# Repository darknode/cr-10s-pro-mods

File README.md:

# Creality CR-10S Pro hardware mods
### Boards
* [Ribbon cable breakdown board](RibbonCable_MB_BreakdownBoard/) - is fully compatible with original transfer board, helps with wiring with non-original motherboards.

* [Ribbon cable breakdown board (pt)](RibbonCable_MB_BreakdownBoard_pt/) - "pig tail" soldering oriented, semi compatible with original transfer board, but fully compatible with [Transfer board](Transfer_Board/). Has dedicated 4-wire connection for BLTouch and 3-wire connector for LED.

* [Transfer board](Transfer_Board/) - clean transfer board, compatible with [Ribbon cable breakdown board (pt)](RibbonCable_MB_BreakdownBoard_pt/).

#### Wiring examples
*Coming soon*

#### Ready made boards
*Photos coming soon*

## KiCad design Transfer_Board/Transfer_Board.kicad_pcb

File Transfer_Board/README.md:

# Transfer board
Clean transfer board, compatible with [Ribbon cable breakdown board (pt)](../RibbonCable_MB_BreakdownBoard_pt/)

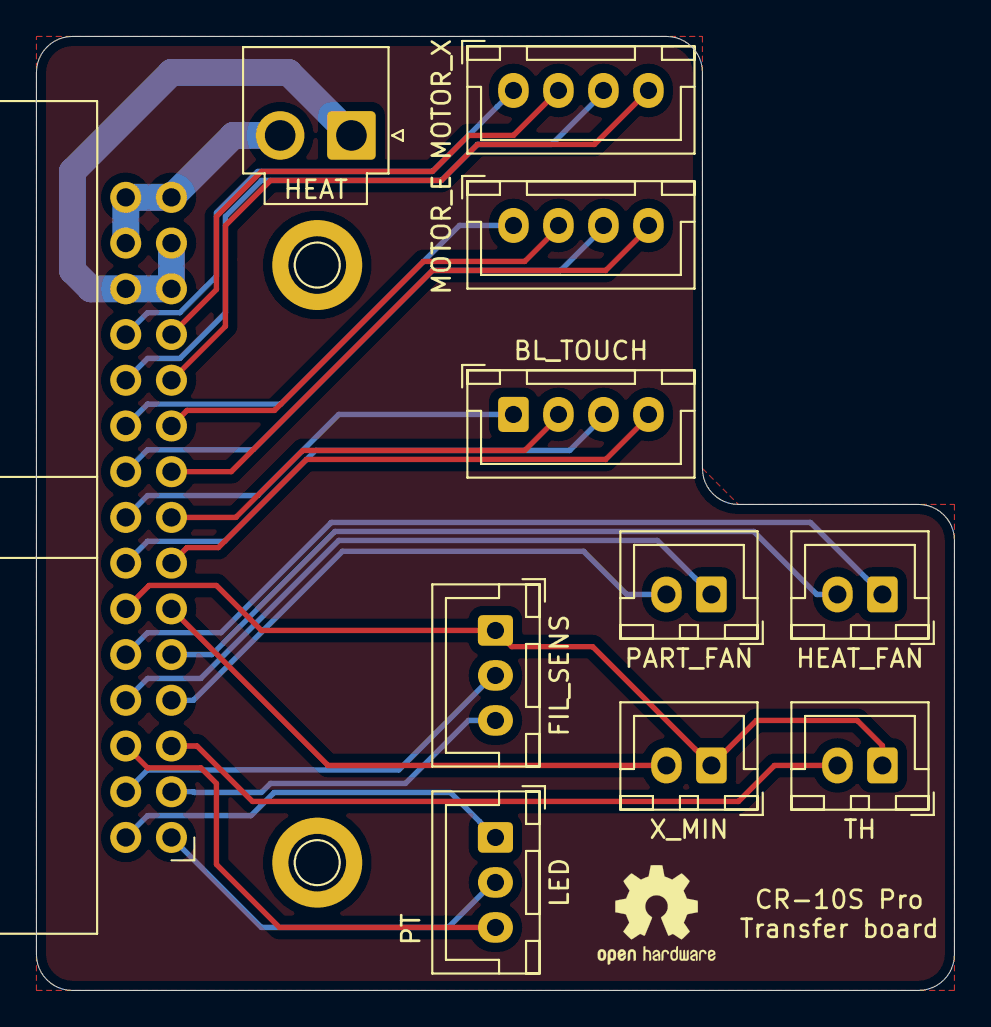
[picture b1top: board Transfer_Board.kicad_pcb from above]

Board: 2 copper layers, 51.0 x 53.0 mm, 11 parts (0 on the bottom side), 26 nets.

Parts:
BL_TOUCH: Conn_01x04; JST_XH_B4B-XH-A_1x04_P2.50mm_Vertical
FIL_SENS: Conn_01x03; JST_XH_B3B-XH-A_1x03_P2.50mm_Vertical
HEAT: Conn_01x02; JST_VH_B2P-VH-B_1x02_P3.96mm_Vertical
HEAT_FAN: Conn_01x02; JST_XH_B2B-XH-A_1x02_P2.50mm_Vertical
LED: Conn_01x03; JST_XH_B3B-XH-A_1x03_P2.50mm_Vertical
MOTOR_E: Conn_01x04; JST_XH_B4B-XH-A_1x04_P2.50mm_Vertical
MOTOR_X: Conn_01x04; JST_XH_B4B-XH-A_1x04_P2.50mm_Vertical
PART_FAN: Conn_01x02; JST_XH_B2B-XH-A_1x02_P2.50mm_Vertical
RIBBON1: Conn_02x15_Odd_Even; IDC-Header_2x15_P2.54mm_Horizontal
TH: Conn_01x02; JST_XH_B2B-XH-A_1x02_P2.50mm_Vertical
X_MIN: Conn_01x02; JST_XH_B2B-XH-A_1x02_P2.50mm_Vertical

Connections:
unnamed: BL_TOUCH.1, RIBBON1.16
unnamed: BL_TOUCH.2, RIBBON1.15
unnamed: BL_TOUCH.3, RIBBON1.14
unnamed: BL_TOUCH.4, RIBBON1.13
unnamed: FIL_SENS.1, RIBBON1.12, TH.1, X_MIN.1
unnamed: FIL_SENS.2, RIBBON1.4
unnamed: FIL_SENS.3, RIBBON1.3
unnamed: HEAT.1, RIBBON1.25, RIBBON1.26, RIBBON1.27
unnamed: HEAT.2, RIBBON1.28, RIBBON1.29, RIBBON1.30
unnamed: HEAT_FAN.1, RIBBON1.10
unnamed: HEAT_FAN.2, RIBBON1.9
unnamed: LED.1, RIBBON1.2
unnamed: LED.2, RIBBON1.1
unnamed: LED.3, RIBBON1.6
unnamed: MOTOR_E.1, RIBBON1.20
unnamed: MOTOR_E.2, RIBBON1.19
unnamed: MOTOR_E.3, RIBBON1.18
unnamed: MOTOR_E.4, RIBBON1.17
unnamed: MOTOR_X.1, RIBBON1.24
unnamed: MOTOR_X.2, RIBBON1.23
unnamed: MOTOR_X.3, RIBBON1.22
unnamed: MOTOR_X.4, RIBBON1.21
unnamed: PART_FAN.1, RIBBON1.8
unnamed: PART_FAN.2, RIBBON1.7
unnamed: RIBBON1.5, TH.2
unnamed: RIBBON1.11, X_MIN.2

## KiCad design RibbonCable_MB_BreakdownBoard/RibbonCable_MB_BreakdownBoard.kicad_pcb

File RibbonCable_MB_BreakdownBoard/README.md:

# Ribbon cable breakdown board
It is fully compatible with [original transfer board](https://www.aliexpress.com/item/33040303019.html), helps with wiring with non-original motherboards.

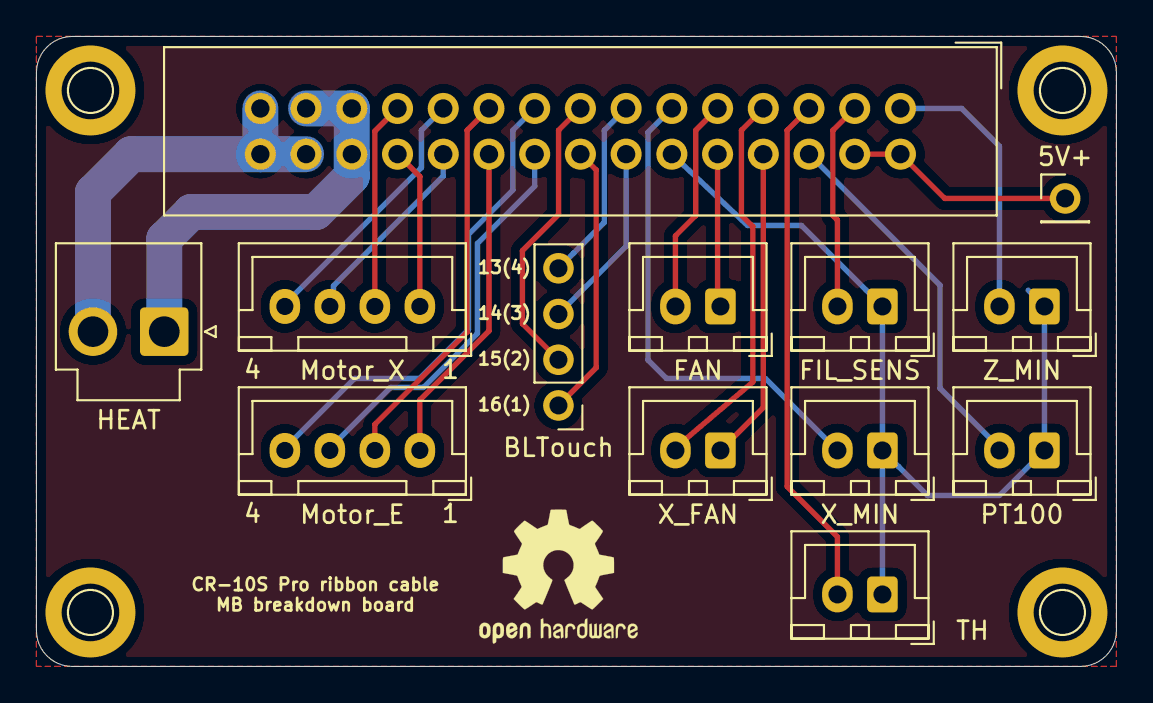
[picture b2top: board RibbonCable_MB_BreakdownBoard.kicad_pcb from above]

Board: 2 copper layers, 60.0 x 35.0 mm, 13 parts (0 on the bottom side), 25 nets.

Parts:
5V+: Conn_01x01; PinHeader_1x01_P2.54mm_Vertical
BLTouch: Conn_01x04; PinHeader_1x04_P2.54mm_Vertical
FAN: Conn_01x02; JST_XH_B2B-XH-A_1x02_P2.50mm_Vertical
FIL_SENS: FIL_SENS; JST_XH_B2B-XH-A_1x02_P2.50mm_Vertical
HEAT: Conn_01x02; JST_VH_B2P-VH-B_1x02_P3.96mm_Vertical
Motor_E: Conn_01x04; JST_XH_B4B-XH-A_1x04_P2.50mm_Vertical
Motor_X: Conn_01x04; JST_XH_B4B-XH-A_1x04_P2.50mm_Vertical
PT100: PT100; JST_XH_B2B-XH-A_1x02_P2.50mm_Vertical
Ribbon1: Ribbon30; IDC-Header_2x15_P2.54mm_Vertical
TH: TH+; JST_XH_B2B-XH-A_1x02_P2.50mm_Vertical
X_FAN: Conn_01x02; JST_XH_B2B-XH-A_1x02_P2.50mm_Vertical
X_MIN: Conn_01x02; JST_XH_B2B-XH-A_1x02_P2.50mm_Vertical
Z_MIN: Z_MIN; JST_XH_B2B-XH-A_1x02_P2.50mm_Vertical

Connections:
/HEAT_GND: HEAT.1, Ribbon1.25, Ribbon1.26, Ribbon1.27
/Heat+: HEAT.2, Ribbon1.28, Ribbon1.29, Ribbon1.30
unnamed: 5V+.1, Ribbon1.2, Ribbon1.4
unnamed: BLTouch.1, Ribbon1.16
unnamed: BLTouch.2, Ribbon1.15
unnamed: BLTouch.3, Ribbon1.14
unnamed: BLTouch.4, Ribbon1.13
unnamed: FAN.1, Ribbon1.10
unnamed: FAN.2, Ribbon1.9
unnamed: FIL_SENS.1, PT100.1, Ribbon1.12, TH.1, X_MIN.1, Z_MIN.1
unnamed: FIL_SENS.2, Ribbon1.3
unnamed: Motor_E.1, Ribbon1.20
unnamed: Motor_E.2, Ribbon1.19
unnamed: Motor_E.3, Ribbon1.18
unnamed: Motor_E.4, Ribbon1.17
unnamed: Motor_X.1, Ribbon1.24
unnamed: Motor_X.2, Ribbon1.23
unnamed: Motor_X.3, Ribbon1.22
unnamed: Motor_X.4, Ribbon1.21
unnamed: PT100.2, Ribbon1.6
unnamed: Ribbon1.1, Z_MIN.2
unnamed: Ribbon1.5, TH.2
unnamed: Ribbon1.7, X_FAN.2
unnamed: Ribbon1.8, X_FAN.1
unnamed: Ribbon1.11, X_MIN.2

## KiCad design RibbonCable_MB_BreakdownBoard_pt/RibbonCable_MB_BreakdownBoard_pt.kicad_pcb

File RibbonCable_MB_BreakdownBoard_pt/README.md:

# Ribbon cable breakdown board "pig tail"
Ts is  "pig tail" soldering oriented, semi compatible with original transfer board, but fully compatible with [Transfer board](../Transfer_Board/). Has dedicated 4-wire connection for BLTouch and 3-wire connector for LED.

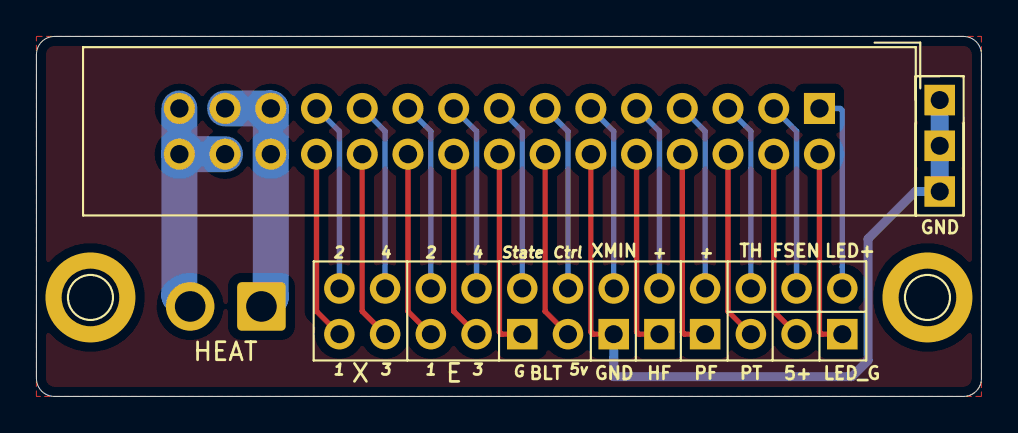
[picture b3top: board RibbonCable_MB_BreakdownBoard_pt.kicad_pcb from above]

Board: 2 copper layers, 52.5 x 20.0 mm, 4 parts (0 on the bottom side), 26 nets.

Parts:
CONN_GND1: Conn_01x03; PinHeader_1x03_P2.54mm_Vertical
HEAT: Conn_01x02; JST_VH_B2P-VH-B_1x02_P3.96mm_Vertical
PIN_HEADER1: Conn_01x24; PinHeader_2x12_P2.54mm_Vertical
Ribbon1: Ribbon30; IDC-Header_2x15_P2.54mm_Vertical

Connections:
/Heat+: HEAT.2, Ribbon1.28, Ribbon1.29, Ribbon1.30
/Heat-: HEAT.1, Ribbon1.25, Ribbon1.26, Ribbon1.27
unnamed: CONN_GND1.1, CONN_GND1.2, CONN_GND1.3, PIN_HEADER1.12, Ribbon1.12
unnamed: PIN_HEADER1.1, Ribbon1.1
unnamed: PIN_HEADER1.2, Ribbon1.2
unnamed: PIN_HEADER1.3, Ribbon1.3
unnamed: PIN_HEADER1.4, Ribbon1.4
unnamed: PIN_HEADER1.5, Ribbon1.5
unnamed: PIN_HEADER1.6, Ribbon1.6
unnamed: PIN_HEADER1.7, Ribbon1.7
unnamed: PIN_HEADER1.8, Ribbon1.8
unnamed: PIN_HEADER1.9, Ribbon1.9
unnamed: PIN_HEADER1.10, Ribbon1.10
unnamed: PIN_HEADER1.11, Ribbon1.11
unnamed: PIN_HEADER1.13, Ribbon1.13
unnamed: PIN_HEADER1.14, Ribbon1.14
unnamed: PIN_HEADER1.15, Ribbon1.15
unnamed: PIN_HEADER1.16, Ribbon1.16
unnamed: PIN_HEADER1.17, Ribbon1.17
unnamed: PIN_HEADER1.18, Ribbon1.18
unnamed: PIN_HEADER1.19, Ribbon1.19
unnamed: PIN_HEADER1.20, Ribbon1.20
unnamed: PIN_HEADER1.21, Ribbon1.21
unnamed: PIN_HEADER1.22, Ribbon1.22
unnamed: PIN_HEADER1.23, Ribbon1.23
unnamed: PIN_HEADER1.24, Ribbon1.24

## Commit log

2019-09-28 RibbonCable MB Breakdown board initial version
2019-10-03 Draft - pigtail version of breakdown board
2019-10-10 Add Transfer board
2019-10-10 New boards
2019-10-10 Fix images in the main readme
